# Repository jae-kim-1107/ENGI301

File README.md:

# ENGI301

Repository for ENGI301 course work

See project_1 for Voice Controlled Car project

See project_2 for PCB for Voice Controlled Car project

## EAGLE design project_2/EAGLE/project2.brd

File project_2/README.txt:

Voice Controlled Car PCB, Jae Hyen Kim

Hello! Thanks for checking out my project!

These are the PCB files (EAGLE schematic, board, layout as well as GERBER files) for my voice-controlled
car project (more details of which can be found here:
https://www.hackster.io/jae-kim2/voice-controlled-toy-car-fcd8af)

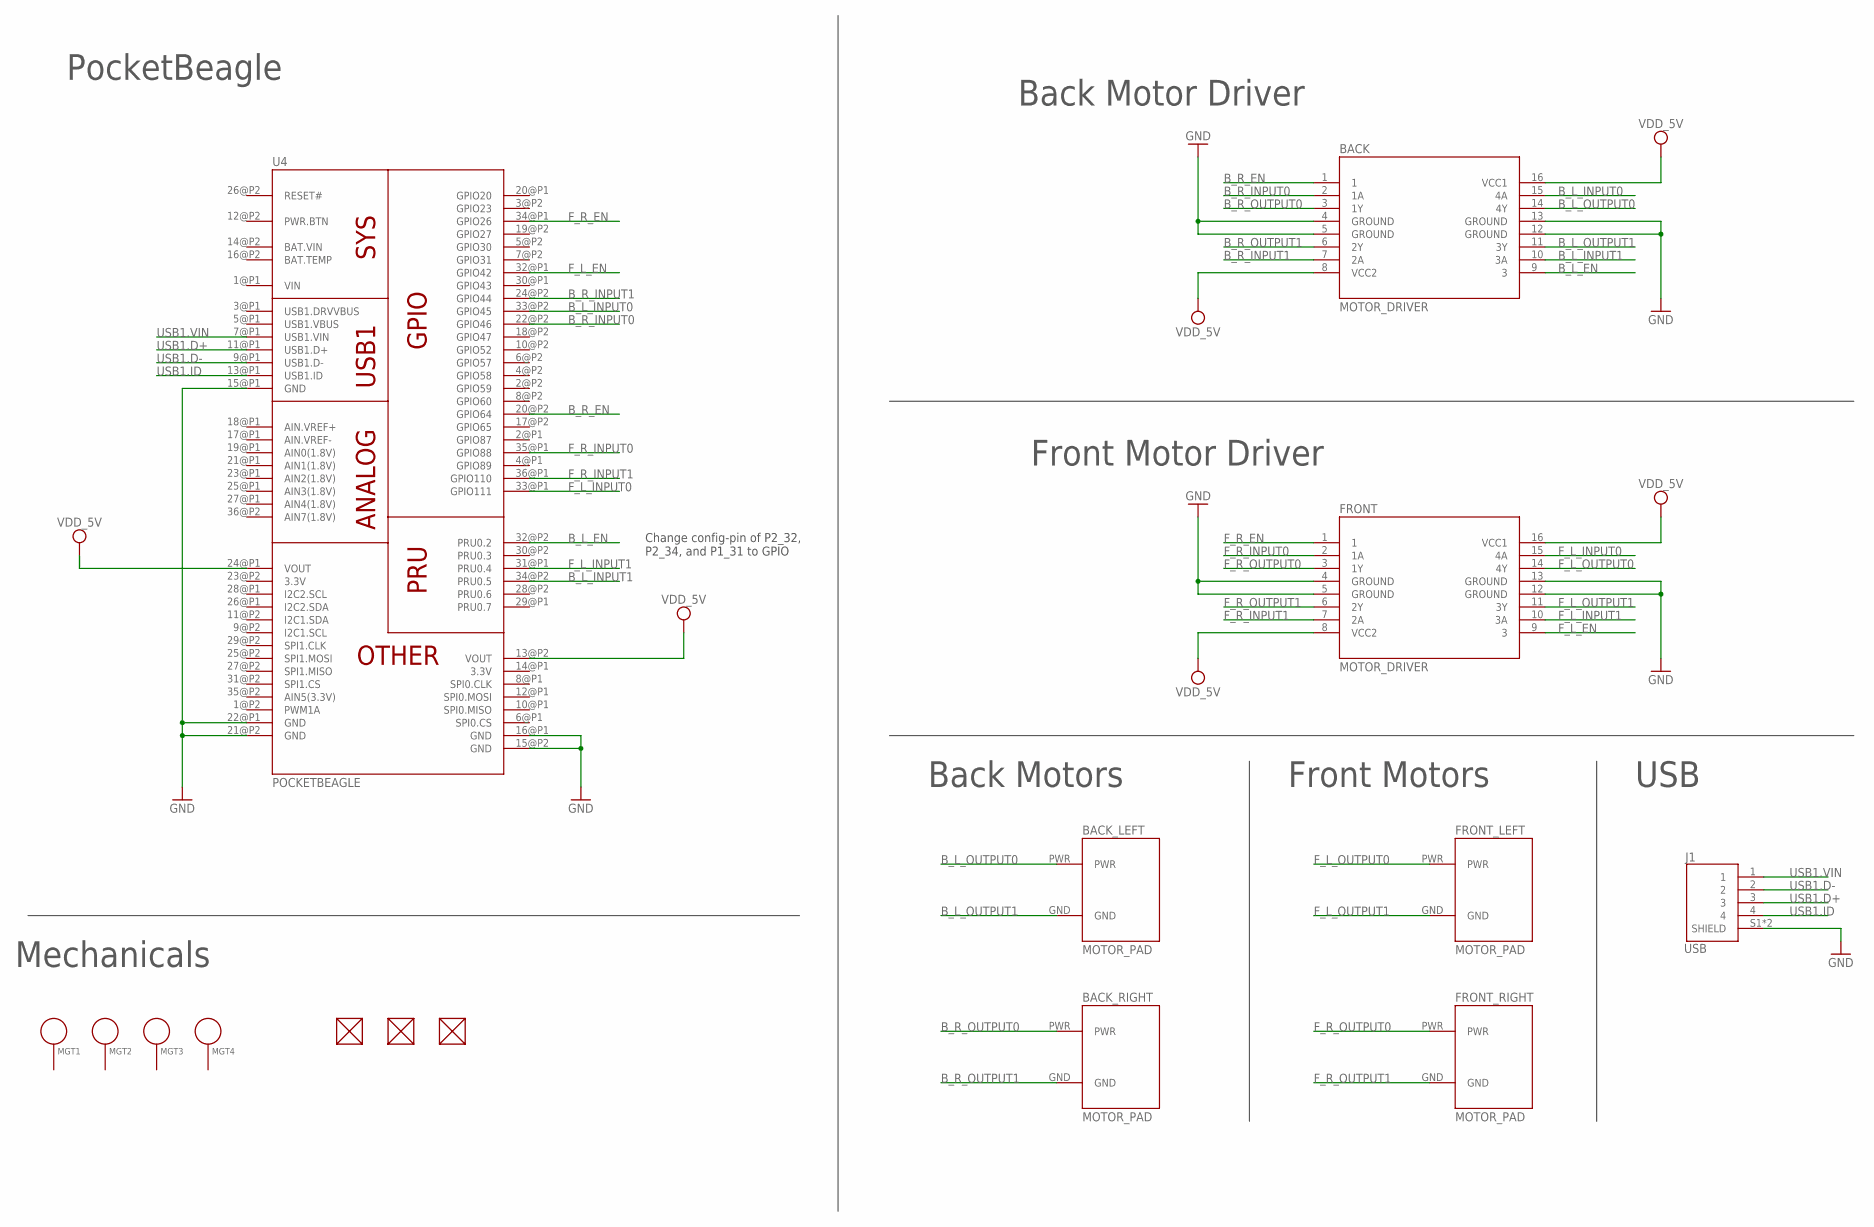
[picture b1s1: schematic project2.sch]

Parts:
BACK: MOTOR_DRIVER
BACK_LEFT: MOTOR_PAD
BACK_RIGHT: MOTOR_PAD
FRONT: MOTOR_DRIVER
FRONT_LEFT: MOTOR_PAD
FRONT_RIGHT: MOTOR_PAD
FUD1, FUD2, FUD3: FIDUCIAL; FIDUCIAL_40MIL
J1: USB; J_SMD_292303-9-4_2,2.5_14.85_14.06_8.9
MGT1, MGT2, MGT3, MGT4: MOUNTING_HOLE
U4: POCKETBEAGLE

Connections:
BAT.VIN: U4.14@P2 (BAT.VIN)
B_L_EN: BACK.9 (3), U4.32@P2 (PRU0.2)
B_L_INPUT0: BACK.15 (4A), U4.33@P2 (GPIO45)
B_L_INPUT1: BACK.10 (3A), U4.34@P2 (PRU0.5)
B_L_OUTPUT0: BACK.14 (4Y), BACK_LEFT.PWR
B_L_OUTPUT1: BACK.11 (3Y), BACK_LEFT.GND
B_R_EN: BACK.1, U4.20@P2 (GPIO64)
B_R_INPUT0: BACK.2 (1A), U4.22@P2 (GPIO46)
B_R_INPUT1: BACK.7 (2A), U4.24@P2 (GPIO44)
B_R_OUTPUT0: BACK.3 (1Y), BACK_RIGHT.PWR
B_R_OUTPUT1: BACK.6 (2Y), BACK_RIGHT.GND
F_L_EN: FRONT.9 (3), U4.32@P1 (GPIO42)
F_L_INPUT0: FRONT.15 (4A), U4.33@P1 (GPIO111)
F_L_INPUT1: FRONT.10 (3A), U4.31@P1 (PRU0.4)
F_L_OUTPUT0: FRONT.14 (4Y), FRONT_LEFT.PWR
F_L_OUTPUT1: FRONT.11 (3Y), FRONT_LEFT.GND
F_R_EN: FRONT.1, U4.34@P1 (GPIO26)
F_R_INPUT0: FRONT.2 (1A), U4.35@P1 (GPIO88)
F_R_INPUT1: FRONT.7 (2A), U4.36@P1 (GPIO110)
F_R_OUTPUT0: FRONT.3 (1Y), FRONT_RIGHT.PWR
F_R_OUTPUT1: FRONT.6 (2Y), FRONT_RIGHT.GND
GND: BACK.4 (GROUND), BACK.5 (GROUND), BACK.12 (GROUND), BACK.13 (GROUND), FRONT.4 (GROUND), FRONT.5 (GROUND), FRONT.12 (GROUND), FRONT.13 (GROUND), J1.S1 (SHIELD), J1.S2 (SHIELD), U4.15@P1 (GND), U4.15@P2 (GND), U4.16@P1 (GND), U4.21@P2 (GND), U4.22@P1 (GND)
USB1.D+: J1.3, U4.11@P1 (USB1.D+)
USB1.D-: J1.2, U4.9@P1 (USB1.D-)
USB1.ID: J1.4, U4.13@P1 (USB1.ID)
USB1.VIN: J1.1, U4.7@P1 (USB1.VIN)
VDD_5V: BACK.8 (VCC2), BACK.16 (VCC1), FRONT.8 (VCC2), FRONT.16 (VCC1), U4.13@P2 (VOUT), U4.24@P1 (VOUT)
VIN: U4.1@P1 (VIN)

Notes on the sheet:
PocketBeagle
Back Motor Driver
Front Motor Driver
Back Motors
Front Motors
USB
Change config-pin of P2_32, P2_34, and P1_31 to GPIO
Mechanicals

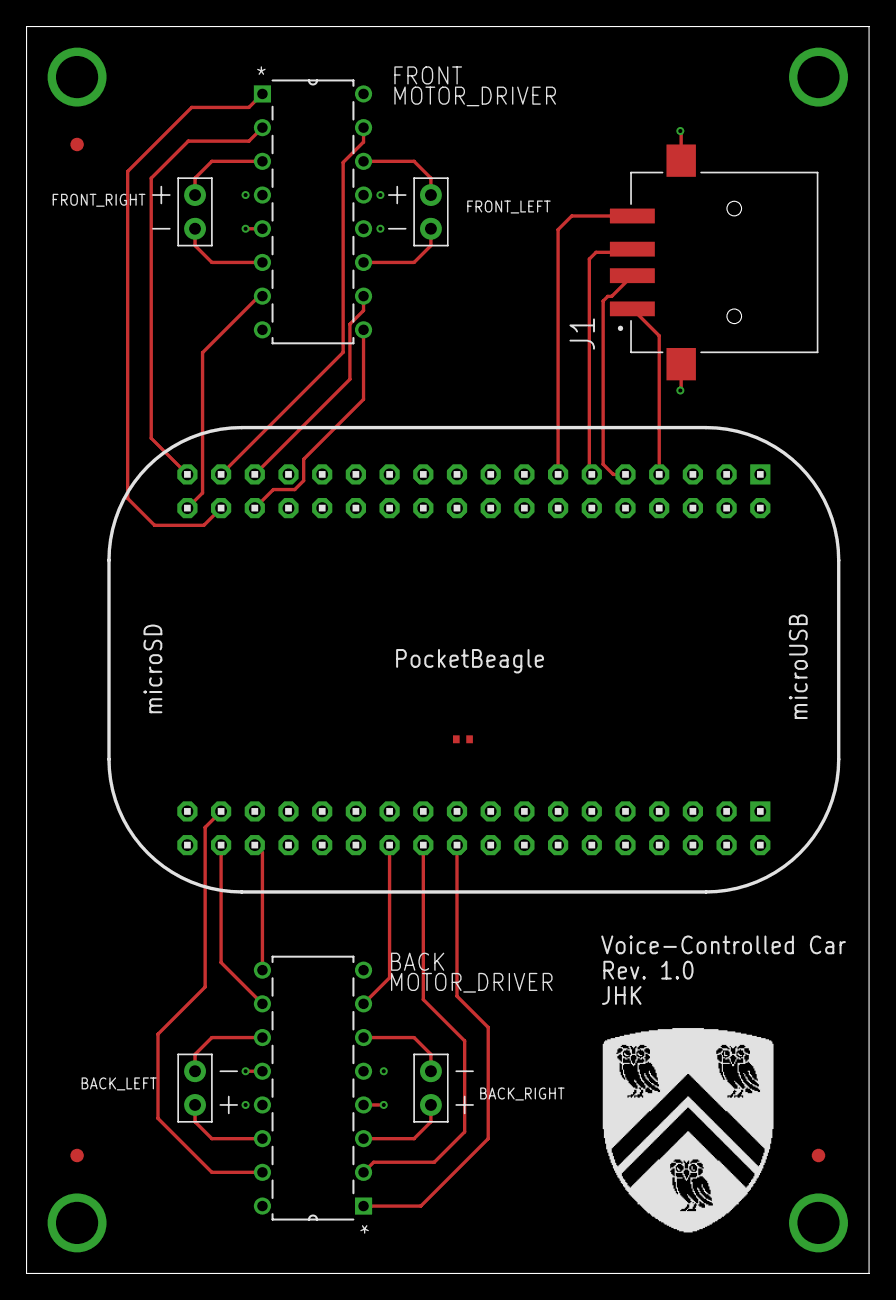
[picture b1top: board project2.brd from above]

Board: 4 copper layers, 63.5 x 94.0 mm, 15 parts (0 on the bottom side), 26 nets.

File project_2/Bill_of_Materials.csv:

Designator,Manufacter/MPN,Quantity,Description
POCKETBEAGLE,POCKETBEAGLE-SC-569,1,USB-key-fob computer
MOTOR_PAD,N/A,4,Connection for motor
MOTOR_DRIVER,L293DNE,2,Quadruple high-current half-H drivers
FIDUCIAL,N/A,3,FIDUCIAL
USB,TE Connectivity 292303-6,1,Surface-mounted USB-A Connector
MOUNTING_HOLE,N/A,4,Holes for mounting

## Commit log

2020-09-14 Update README.md
    Updating README.md
2020-09-29 Create simple_calc.py
    created directory python/simple_calc and copied in simple calculator done in class
2020-09-29 created simple_calc modified and blink_USR3
    created simple_calc modified
    created blink_USR3
2020-10-07 Create JaeKim_ProjectProposal.pptx
    added project_1 folder and proposal document
2020-10-15 updated project proposal
2020-11-12 project started and motors tested
2020-11-12 added stop, forward, backward, and turn left to motor control
2020-11-12 added turn right, backward
2020-11-12 made speech
2020-11-12 Added run file, made sure everything worked
2020-11-14 Added README
2020-11-23 Created project 2 proposal
2020-12-19 finished project 2 files
2020-12-19 added bill of materials csv
2021-03-23 Update README.md
    updated README
